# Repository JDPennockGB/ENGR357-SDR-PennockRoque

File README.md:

# ENGR 357 Pico SDR Receiver

A custom-built, high-performance Software Defined Radio (SDR) receiver powered by the Raspberry Pi Pico (RP2040). This project combines a classic hardware Tayloe detector with modern digital signal processing, streaming 24-bit I/Q audio and CAT control over a single USB cable directly to PC-based SDR software like **Quisk**.

GitHub Link: https://github.com/JDPennockGB/ENGR357-SDR-PennockRoque 

---

## Overview

Traditional homebrew SDR receivers often rely on routing analog audio cables into a PC soundcard, which can introduce noise and ground loops. This project solves that by digitizing the baseband I/Q signals directly on the board using a dedicated 24-bit ADC, and utilizing the RP2040's hardware PIO and TinyUSB stack to act as a **Composite CDC-UAC1 USB Device**. 

When plugged into a computer, this radio appears simultaneously as:
1. **USB Audio Class 2.0 (UAC2) Input:** Streaming ultra-clean 24-bit stereo I/Q audio to the PC.
2. **USB CDC Serial Port:** Receiving standard CAT tuning commands from the SDR software.

## Key Features

ADD FEATURES

---

## Hardware
### Overview
* **MCU:** Raspberry Pi Pico (RP2040) utilizing PIO and DMA for zero-jitter data handling.
* **Clock Generator:** Si5351A providing precise LO generation and the 12.288 MHz Master Clock (MCLK) for the ADC.
* **Quadrature Generator:** SN74AC74 Johnson counter for exact 90-degree I/Q phase shifting.
* **Mixer (Tayloe Detector):** SN74CBT3253 Quadrature Sampling Detector.
* **Baseband Amplification:** OPA2350 high-speed, low-noise operational amplifiers.
* **Digitization:** PCM1808 24-bit Stereo I2S ADC.
* **User Interface:** * Newhaven 1x8 Character LCD (ST7066U / 3.3V)
  * Quadrature Rotary Encoder with push-button for VFO tuning
  * 4x SMD Push Buttons for menu/mode navigation (not currently implemented in software)

### Pinout Configuration
The following table outlines the physical connections between the Raspberry Pi Pico and your hardware components.

| Pin | Function | Connected | Implemented |
| :--- | :--- | :---: | :---: |
| **GPIO0** | BCK | ✅ | ❌ |
| **GPIO1** | WS | ✅ | ❌ |
| **GPIO2** | DOUT | ✅ | ❌ |
| **GPIO11** | SD | ✅ | ❌ |
| **GPIO3** | LCD_Bit0 | ✅ | ✅ |
| **GPIO4** | LCD_Bit1 | ✅ | ✅ |
| **GPIO5** | LCD_Bit2 | ✅ | ✅ |
| **GPIO6** | LCD_Bit3 | ✅ | ✅ |
| **GPIO7** | LCD_Bit4 | ✅ | ✅ |
| **GPIO8** | LCD_Bit5 | ✅ | ✅ |
| **GPIO9** | LCD_Bit6 | ✅ | ✅ |
| **GPIO10** | LCD_Bit7 | ✅ | ✅ |
| **GPIO12** | I2C Bus SDA | ✅ | ✅ |
| **GPIO13** | I2C Bus SCL | ✅ | ✅ |
| **GPIO14** | LCD_RegSel | ✅ | ✅ |
| **GPIO15** | LCD_Ena | ✅ | ✅ |
| **GPIO16** | Up_Btn | ✅ | ❌ |
| **GPIO17** | Left_Btn | ✅ | ❌ |
| **GPIO18** | Select_Btn | ✅ | ❌ |
| **GPIO19** | Right_Btn | ✅ | ❌ |
| **GPIO20** | Encoder_A | ✅ | ✅ |
| **GPIO21** | Encoder_B | ✅ | ✅ |
| **GPIO22** | Encoder_Button| ✅ | ❌ |
| **GPIO26** | ADC0 (I_OUT) | ❌ | ❌ |
| **GPIO27** | ADC1 (Q_OUT) | ❌ | ❌ |
| **AGND** | GND | ✅ | ✅ |
| **VBUS** | +5v Bus | ✅ | ✅ |
| **3v3** | +3.3v Bus | ✅ | ✅ |

---

## Software
### Overview
* **Framework:** C/C++ via the Raspberry Pi Pico SDK.
* **USB Stack:** TinyUSB configured for a unidirectional composite UAC1 Capture + CDC interface.
* **DSP Pipeline:** Custom PIO state machines reading I2S data, fed via DMA directly to USB buffers without bottlenecking the CPU.

### Function Reference

#### LCD Driver (`lcd_driver.c`)
Manages the 8-bit parallel interface for the ST7066U controller.

| Function | Description |
| :--- | :--- |
| `void lcd_init()` | [cite_start]Executes the power-on initialization routine, including the 3-step "Wake up" sequence required for the ST7066U controller to stabilize[cite: 259]. |
| `void lcd_command(uint8_t cmd)` | Sets the `RS` (Register Select) pin LOW for command mode, drives the 8-bit bus, and toggles the `E` (Enable) pin to latch data. |
| `void lcd_clear()` | [cite_start]Sends the `0x01` instruction to clear the display RAM and reset the cursor[cite: 178]. |
| `void lcd_print(const char* str)` | Sets `RS` HIGH for data mode, iterates through the string, and writes character bytes to the LCD data bus. |

#### Clock Synthesizer (`si5351.c`)
Interfaces with the Si5351 via I2C for frequency generation.

| Function | Description |
| :--- | :--- |
| `bool si5351_init(i2c_inst_t *i2c)` | [cite_start]Initializes I2C, verifies device status, and loads factory crystal load settings[cite: 172]. |
| `uint32_t si5351_set_frequency(...)` | Calculates PLL and MultiSynth divisors, programs the register blocks, resets the PLL to achieve frequency lock, and enables the output clock. |

#### Command & Control (`cdc_app.c` & `main.c`)
Handles communication and system state.

| Function | Description |
| :--- | :--- |
| `void cdc_task()` | Parses incoming serial data for Quisk-compatible commands (e.g., `FREQ`, `VER`, `XTAL`), enabling remote control of the SDR. |
| `static void process_command(const char *line)` | Dispatcher function that maps string commands (like `FREQ`) to specific hardware actions. |
| `void audio_task()` | Handles the audio buffer from the DMA/FIFO into the USB streaming interface. |
| `void encoder_callback(...)` | ISR that tracks encoder rotation to update the `current_hz` variable, which is then processed by the main loop. |

### Build Instructions
1. **Prerequisites**: Ensure the `Pico SDK` abd `TinyUSB` libraries are installed
2. **Setup**:
   ```bash
   cd /path/to/sdr-firmware
   rm -rf build && mkdir build && cd build

---

## Repository Structure

This repository contains the hardware design files, the C/C++ firmware, Python unit tests, and relevant research documentation.

ENGR-357-SDR/

├── Documents/              # Research notes, datasheets, and design requirements

├── KiCad Designs/          # PCB schematics, layout files, and BOMs

│   ├── v1 Switch Mixer/

│   ├── v2 Tayloe Detector/

│   └── v3 Tayloe Detector FINAL/

├── LT Spice Simulations/   # RF demodulator analysis and circuit models

│   ├── LTSpice project files/

│   └── Simulation Results/ # Images of simulation results

└── sdr-firmware/           # RP2040 Firmware (Pico SDK)

    ├── build/              # Compiled binaries and artifacts

    ├── PythonUnitTests/    # Verification and testing scripts

    └── main.c + drivers                # C firmware source files

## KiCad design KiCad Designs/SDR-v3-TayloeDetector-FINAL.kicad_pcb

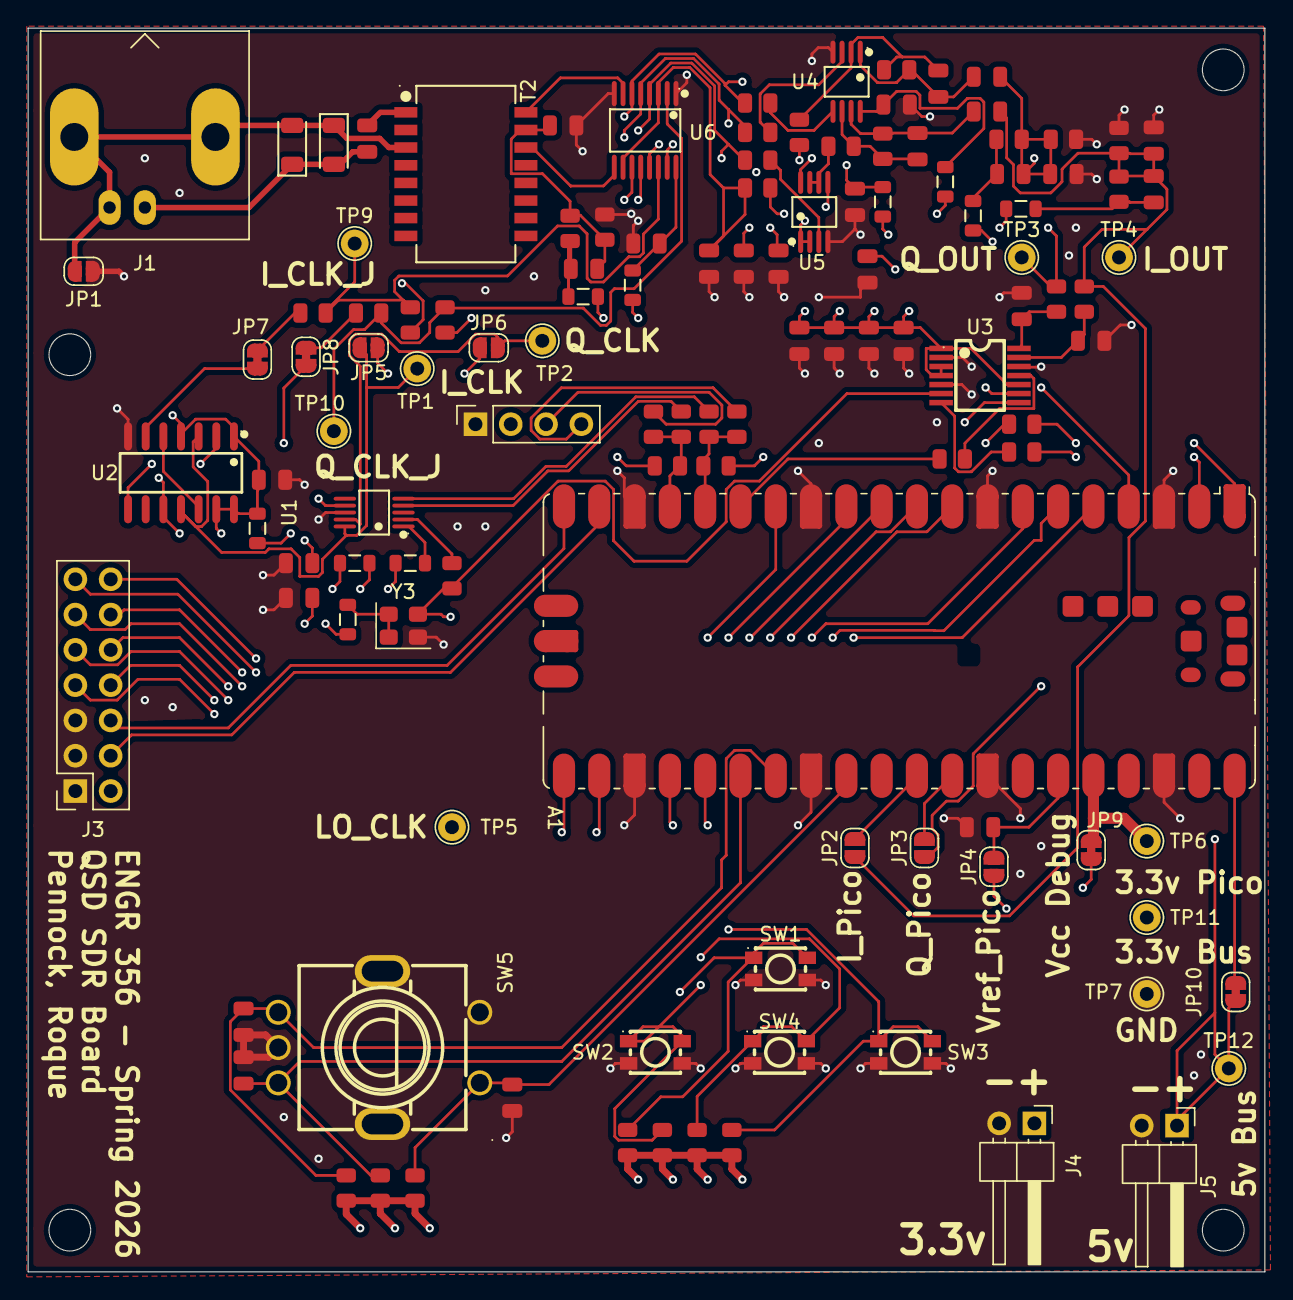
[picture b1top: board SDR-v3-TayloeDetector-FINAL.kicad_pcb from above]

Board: 4 copper layers, 89.0 x 89.5 mm, 120 parts (0 on the bottom side), 85 nets.

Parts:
A1: RaspberryPi_Pico; RaspberryPi_Pico_SMD
C1, C2, C3, C4, C9, C12, C13, C18, C19, C20, C21, C27, C29, C32, C33, C35: 10uF; C_0805
C5, C6, C7, C8: 10nF; C_0805
C10, C11: 47pF; C_0805
C16, C17: 1uF; C_0805
C23, C24, C28, C30, C31: 100nF; C_0805
C25, C34: 2.2nF; C_0805
D1, D2: 1N4004W; D_SOD-123FL
FB11, FB12, FB13, FB14, FB15, FB16, FB17, FB18, FB19, FB20: FB_0805
J1: Antenna; BNC_Amphenol_B6252HB-NPP3G-50_Horizontal
J2: OLED Header; PinSocket_1x04_P2.54mm_Vertical
J3: 1x8 LCD Header; PinSocket_2x07_P2.54mm_Vertical
J4, J5: BackupVCC (+3.3v); PinHeader_1x02_P2.54mm_Horizontal
JP1: Antenna2GND; SolderJumper-2_P1.3mm_Open_RoundedPad1.0x1.5mm
JP2: I2PicoADC; SolderJumper-2_P1.3mm_Open_RoundedPad1.0x1.5mm
JP3: Q2PicoADC; SolderJumper-2_P1.3mm_Open_RoundedPad1.0x1.5mm
JP4: PicoADCVref; SolderJumper-2_P1.3mm_Open_RoundedPad1.0x1.5mm
JP5: I_CLK_nonJ; SolderJumper-2_P1.3mm_Open_RoundedPad1.0x1.5mm
JP6: Q_CLK_nonJ; SolderJumper-2_P1.3mm_Open_RoundedPad1.0x1.5mm
JP7: I_CLK_Johnson; SolderJumper-2_P1.3mm_Bridged_RoundedPad1.0x1.5mm
JP8: Q_CLK_Johnson; SolderJumper-2_P1.3mm_Bridged_RoundedPad1.0x1.5mm
JP9: 3.3v_Pico2Bus; SolderJumper-2_P1.3mm_Bridged_RoundedPad1.0x1.5mm
JP10: 5vPicoBus; SolderJumper-2_P1.3mm_Bridged_RoundedPad1.0x1.5mm
R1, R2, R3, R4: 10Ω; R_0805
R5, R6: 47Ω; R_0805
R7, R8: 1.5kΩ; R_0805
R9, R10, R11, R12, R13, R14, R16, R24: 33Ω; R_0805
R15, R23: 470Ω; R_0805
R17, R18, R19, R20: 100Ω; R_0805
R21, R22: 4.7kΩ; R_0805
R36, R37, R38, R39, R40, R41, R42, R43, R44, R45, R46, R47, R48: 10kΩ; R_0805
SW1, SW2, SW3, SW4: TS-1185-W-4P-H1.8-160; SW-SMD_4P-L3.5-W3.0-P1.50-LS4.7
SW5: EC11E18244AU; SW-TH_EC11XXXXXXXX
T2: H1102NLT_C20623173; XFMR-SMD_H1102NLT
TP1: I_CLK; TestPoint_THTPad_D2.0mm_Drill1.0mm
TP2: Q_CLK; TestPoint_THTPad_D2.0mm_Drill1.0mm
TP3: Q_OUT; TestPoint_THTPad_D2.0mm_Drill1.0mm
TP4: I_OUT; TestPoint_THTPad_D2.0mm_Drill1.0mm
TP5: LO_CLK; TestPoint_THTPad_D2.0mm_Drill1.0mm
TP6: +3.3V_Pico; TestPoint_THTPad_D2.0mm_Drill1.0mm
TP7: GND; TestPoint_THTPad_D2.0mm_Drill1.0mm
TP9: I_CLK_J; TestPoint_THTPad_D2.0mm_Drill1.0mm
TP10: Q_CLK_J; TestPoint_THTPad_D2.0mm_Drill1.0mm
TP11: +3.3V_bus; TestPoint_THTPad_D2.0mm_Drill1.0mm
TP12: +5V_bus; TestPoint_THTPad_D2.0mm_Drill1.0mm
U1: SI5351A-B-GT; MSOP-10_L3.0-W3.0-P0.50-LS5.0-BL
U2: SN74AC74DR; SOIC-14_L8.7-W3.9-P1.27-LS6.0-BL
U3: PCM1808PWR; TSSOP-14_L5.0-W4.4-P0.65-LS6.4-BL
U4, U5: OPA2350EA/250; VSSOP-8_L3.0-W3.0-P0.65-LS5.0-BL
U6: SN74CBT3253DBQR; SSOP-16_L4.9-W3.9-P0.64-LS6.0-BL
Y3: ASE-xxxMHz; Oscillator_SMD_Abracon_ASE-4Pin_3.2x2.5mm

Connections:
+3.3V: C27.2, C28.1, C29.2, C30.1, C32.2, C33.2, FB11.1, FB13.1, FB14.1, FB15.1, FB16.1, FB17.1, FB18.1, FB19.1, FB20.1, J2.2, J3.2, J4.1, JP4.1 (A), JP9.1 (A), R21.1, R22.1, R42.2, R43.2, R44.2, R45.2, R46.2, R47.2, R48.2, TP11.1 (1_1), U3.1 (VREF), U3.3 (VCC), U3.4 (VDD), U3.10 (MD0)
+5V: FB12.1, J5.1, JP10.2 (B), TP12.1 (1_1)
/BCK: A1.1 (GPIO0), R10.2
/DOUT: A1.4 (GPIO2), U3.9 (DOUT)
/Enc_A: A1.26 (GPIO20), C24.1, R47.1, SW5.B
/Enc_B: A1.27 (GPIO21), C23.1, R48.1, SW5.A
/Enc_Sw: A1.29 (GPIO22), C31.1, R46.1, SW5.E
/GPIO12: A1.16 (GPIO12), R17.2, R20.2, R22.2
/GPIO13: A1.17 (GPIO13), R18.2, R19.2, R21.2
/I_CLK: R11.2, R16.1, TP9.1 (1_1), U6.14 (S0)
/I_OUT: C17.2, C20.2, C21.2, JP2.1 (A), R15.1, R40.2, R41.1, TP4.1 (1_1)
/LCD_Bit0: A1.5 (GPIO3), J3.7
/LCD_Bit1: A1.6 (GPIO4), J3.8
/LCD_Bit2: A1.7 (GPIO5), J3.9
/LCD_Bit3: A1.9 (GPIO6), J3.10
/LCD_Bit4: A1.10 (GPIO7), J3.11
/LCD_Bit5: A1.11 (GPIO8), J3.12
/LCD_Bit6: A1.12 (GPIO9), J3.13
/LCD_Bit7: A1.14 (GPIO10), J3.14
/LCD_Ena: A1.20 (GPIO15), J3.6
/LCD_RegSel: A1.19 (GPIO14), J3.4
/LO_CLK: R13.1, TP5.1 (1_1), U3.6 (SCKI), Y3.3 (OUT)
/Left_Btn: A1.22 (GPIO17), R43.1, SW2.1, SW2.2
/OSC_SCL: R18.1, U1.4 (SCL)
/OSC_SDA: R17.1, U1.5 (SDA)
/Q_CLK: R12.2, R24.2, TP10.1 (1_1), U6.2 (S1)
/Q_OUT: C16.2, C18.1, C19.1, JP3.1 (A), R23.1, R36.2, R39.1, TP3.1 (1_1)
/Right_Btn: A1.25 (GPIO19), R44.1, SW3.1, SW3.2
/SCL: J2.3, R19.1
/SD: A1.15 (GPIO11), R9.2
/SDA: J2.4, R20.1
/Select_Btn: A1.24 (GPIO18), R45.1, SW4.1, SW4.2
/Up_Btn: A1.21 (GPIO16), R42.1, SW1.1, SW1.2
/WS: A1.2 (GPIO1), R14.2
GND: A1.3 (GND), A1.8 (GND), A1.13 (GND), A1.18 (GND), A1.23 (GND), A1.28 (GND), A1.33 (AGND), A1.38 (GND), C3.2, C4.2, C5.2, C6.2, C7.2, C8.2, C9.2, C12.2, C13.2, C19.2, C20.1, C23.2, C24.2, C25.2, C27.1, C28.2, C29.1, C30.2, C31.2, C32.1, C33.1, C34.2, C35.1, J2.1, J3.1, J3.3, J3.5, J4.2, J5.2, JP1.2 (B), R38.2, R39.2, R40.1, SW1.3, SW1.4, SW2.3, SW2.4, SW3.3, SW3.4, SW4.3, SW4.4, SW5.6, SW5.7, SW5.C, SW5.D, TP7.1 (1_1), U1.8 (GND), U2.7 (GND), U3.2 (AGND), U3.5 (DGND), U3.12 (FMT), U4.4 (V-), U5.4 (V-), U6.1 (~1OE), U6.8 (GND), U6.15 (~2OE), Y3.2 (GND)
unnamed: A1.36 (3V3), JP9.2 (B), TP6.1 (1_1)
unnamed: A1.35 (ADC_VREF), C35.2, JP4.2 (B)
unnamed: A1.31 (GPIO26_ADC0), JP2.2 (B)
unnamed: A1.32 (GPIO27_ADC1), JP3.2 (B)
unnamed: A1.40 (VBUS), JP10.1 (A)
unnamed: C1.2, T2.1
unnamed: C2.1, C3.1, R37.2, R38.1, T2.15
unnamed: C2.2, FB11.2, R37.1
unnamed: C10.2, C16.1, R7.2, U4.1
unnamed: C11.2, C17.1, R8.2, U4.7
unnamed: C18.2, FB15.2, R36.1
unnamed: C21.1, FB16.2, R41.2
unnamed: D1.1, D2.2, J1.2 (Ext), JP1.1 (A), T2.3
unnamed: C1.1, D1.2, D2.1, J1.1 (In)
unnamed: JP5.1 (A), R11.1
unnamed: JP5.2 (B), TP1.1 (1_1), U1.10 (CLK0), U2.3 (1CLK), U2.11 (2CLK)
unnamed: JP6.1 (A), R12.1
unnamed: JP6.2 (B), TP2.1 (1_1), U1.9 (CLK1)
unnamed: JP7.1 (A), R16.2
unnamed: JP7.2 (B), U2.6 (~1Q)
unnamed: JP8.1 (A), R24.1
unnamed: JP8.2 (B), U2.2 (1D), U2.8 (~2Q)
unnamed: FB18.2, U1.1 (VDD)
unnamed: FB19.2, U1.7 (VDDO)
unnamed: R13.2, U1.2 (XA)
unnamed: U2.5 (1Q), U2.12 (2D)
unnamed: C13.1, FB20.2, U2.1 (~1CLR), U2.4 (~1PRE), U2.10 (~2PRE), U2.13 (~2CLR), U2.14 (VCC)
unnamed: R10.1, U3.8 (BCK)
unnamed: R14.1, U3.7 (LRCK)
unnamed: R9.1, U3.11 (MD1)
unnamed: C25.1, R15.2, U3.13 (VINL)
unnamed: C34.1, R23.2, U3.14 (VINR)
unnamed: R2.2, U4.3 (+)
unnamed: C10.1, R5.2, R7.1, U4.2 (-)
unnamed: R1.2, U4.5 (+)
unnamed: C11.1, R6.2, R8.1, U4.6 (-)
unnamed: C12.1, FB14.2, U4.8 (V+)
unnamed: R3.2, U5.3 (+)
unnamed: R5.1, U5.1, U5.2 (-)
unnamed: R4.2, U5.5 (+)
unnamed: R6.1, U5.6 (-), U5.7
unnamed: C9.1, FB13.2, U5.8 (V+)
unnamed: T2.16, U6.7 (1A)
unnamed: C5.1, R1.1, U6.6 (1B1), U6.13 (2B4)
unnamed: C6.1, R2.1, U6.5 (1B2), U6.12 (2B3)
unnamed: C7.1, R3.1, U6.4 (1B3), U6.11 (2B2)
unnamed: C8.1, R4.1, U6.3 (1B4), U6.10 (2B1)
unnamed: T2.14, U6.9 (2A)
unnamed: C4.1, FB12.2, U6.16 (VCC)
unnamed: FB17.2, Y3.1 (EN), Y3.4 (Vdd)

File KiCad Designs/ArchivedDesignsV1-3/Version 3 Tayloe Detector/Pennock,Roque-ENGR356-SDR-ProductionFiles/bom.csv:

Designator,Footprint,Quantity,Value,LCSC Part #
A1,RaspberryPi_Pico_SMD,1,RaspberryPi_Pico,C7203002
"C1, C12, C13, C18, C19, C2, C20, C21, C27, C29, C3, C32, C33, C35, C4, C9",C_0805,16,10uF,C440198
"C10, C11",C_0805,2,47pF,C14857
"C16, C17",C_0805,2,1uF,C28323
"C23, C24, C28, C30, C31",C_0805,5,100nF,C28233
"C25, C34",C_0805,2,2.2nF,C28260
"C5, C6, C7, C8",C_0805,4,10nF,C1710
"D1, D2",D_SOD-123FL,2,1N4004W,C18199087
"FB11, FB12, FB13, FB14, FB15, FB16, FB17, FB18, FB19, FB20",FB_0805,10,~,C1017
J1,BNC_Amphenol_B6252HB-NPP3G-50_Horizontal,1,Antenna,
J2,PinSocket_1x04_P2.54mm_Vertical,1,OLED Header,
J3,PinSocket_2x07_P2.54mm_Vertical,1,1x8 LCD Header,
"J4, J5",PinHeader_1x02_P2.54mm_Horizontal,2,BackupVCC (+3.3v),
"R1, R2, R3, R4",R_0805,4,10Ω,C17415
"R10, R11, R12, R13, R14, R16, R24, R9",R_0805,8,33Ω,C17634
"R15, R23",R_0805,2,470Ω,C17710
"R17, R18, R19, R20",R_0805,4,100Ω,C17408
"R21, R22",R_0805,2,4.7kΩ,C17673
"R36, R37, R38, R39, R40, R41, R42, R43, R44, R45, R46, R47, R48",R_0805,13,10kΩ,C17414
"R5, R6",R_0805,2,47Ω,C17714
"R7, R8",R_0805,2,1.5kΩ,C4310
"SW1, SW2, SW3, SW4",SW-SMD_4P-L3.5-W3.0-P1.50-LS4.7,4,TS-1185-W-4P-H1.8-160,C51927445
SW5,SW-TH_EC11XXXXXXXX,1,EC11E18244AU,C202365
T2,XFMR-SMD_H1102NLT,1,H1102NLT_C20623173,C20623173
TP1,TestPoint_THTPad_D2.0mm_Drill1.0mm,1,I_CLK,
TP10,TestPoint_THTPad_D2.0mm_Drill1.0mm,1,Q_CLK_J,
TP11,TestPoint_THTPad_D2.0mm_Drill1.0mm,1,+3.3V_bus,
TP12,TestPoint_THTPad_D2.0mm_Drill1.0mm,1,+5V_bus,
TP2,TestPoint_THTPad_D2.0mm_Drill1.0mm,1,Q_CLK,
TP3,TestPoint_THTPad_D2.0mm_Drill1.0mm,1,Q_OUT,
TP4,TestPoint_THTPad_D2.0mm_Drill1.0mm,1,I_OUT,
TP5,TestPoint_THTPad_D2.0mm_Drill1.0mm,1,LO_CLK,
TP6,TestPoint_THTPad_D2.0mm_Drill1.0mm,1,+3.3V_Pico,
TP7,TestPoint_THTPad_D2.0mm_Drill1.0mm,1,GND,
TP9,TestPoint_THTPad_D2.0mm_Drill1.0mm,1,I_CLK_J,
U1,MSOP-10_L3.0-W3.0-P0.50-LS5.0-BL,1,SI5351A-B-GT,C529366
U2,SOIC-14_L8.7-W3.9-P1.27-LS6.0-BL,1,SN74AC74DR,C352945
U3,TSSOP-14_L5.0-W4.4-P0.65-LS6.4-BL,1,PCM1808PWR,C55513
"U4, U5",VSSOP-8_L3.0-W3.0-P0.65-LS5.0-BL,2,OPA2350EA/250,C115876
U6,SSOP-16_L4.9-W3.9-P0.64-LS6.0-BL,1,SN74CBT3253DBQR,C2674552
Y3,Oscillator_SMD_Abracon_ASE-4Pin_3.2x2.5mm,1,ASE-xxxMHz,C52204801

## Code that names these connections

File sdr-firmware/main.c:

/**
 * SDR Controller - Main Firmware
 * Pinout Configured: DOUT=GPIO2, SD=GPIO11, LCD=GPIO3-10,14,15
 */

  // fixed verson for new drivers

#include <stdio.h>
#include <string.h>
#include <stdint.h>
#include "pico/stdlib.h"
#include "pico/multicore.h"
#include "hardware/pio.h"
#include "hardware/dma.h"
#include "hardware/irq.h"
#include "hardware/i2c.h"
#include "tusb.h"
#include "bsp/board.h"
#include "i2s_rx.pio.h"
#include "si5351.h"
#include "lcd_driver.h"
#include "class/audio/audio_device.h"

// --- Hardware Pins ---
#define ENC_A_PIN    20
#define ENC_B_PIN    21
#define LED_PIN      25
#define I2C_SDA_PIN  12
#define I2C_SCL_PIN  13
#define I2S_DATA_PIN 2    // DOUT
#define I2S_BCK_PIN  0
#define I2S_WS_PIN   1

// --- State Variables ---
static volatile uint32_t current_hz = 5680000; 
static volatile bool frequency_changed = true;
static bool sentinel_sent = false;

static uint8_t  s_audio_alt      = 0;
static uint32_t s_sample_rate_hz = 48000U;
static uint8_t  s_mute[3]        = {0, 0, 0}; 

// --- DMA & Audio Buffers ---
#define SINGLE_BUFFER_SIZE  768             
#define WORDS_PER_BUF       (SINGLE_BUFFER_SIZE / 4)  
static uint32_t buf_a[WORDS_PER_BUF];
static uint32_t buf_b[WORDS_PER_BUF];
static uint dma_chan_a, dma_chan_b;

// --- ISRs ---
static void __not_in_flash_func(dma_handler)(void) {
    const uint32_t *filled_buf;
    if (dma_channel_get_irq0_status(dma_chan_a)) {
        dma_channel_acknowledge_irq0(dma_chan_a);
        filled_buf = buf_a;
        dma_channel_set_write_addr(dma_chan_a, buf_a, false);
    } else if (dma_channel_get_irq0_status(dma_chan_b)) {
        dma_channel_acknowledge_irq0(dma_chan_b);
        filled_buf = buf_b;
        dma_channel_set_write_addr(dma_chan_b, buf_b, false);
    } else return;
    multicore_fifo_push_timeout_us((uint32_t)(uintptr_t)filled_buf, 0);
}

void encoder_callback(uint gpio, uint32_t events) {
    if (gpio == ENC_A_PIN) {
        if (gpio_get(ENC_B_PIN)) current_hz += 40000;
        else current_hz -= 40000;
        frequency_changed = true;
    }
}

// --- Tasks ---
static void core1_entry(void) {
    multicore_fifo_drain();               
    irq_clear(DMA_IRQ_0);
    dma_channel_set_irq0_enabled(dma_chan_a, true);
    dma_channel_set_irq0_enabled(dma_chan_b, true);
    irq_set_exclusive_handler(DMA_IRQ_0, dma_handler);
    irq_set_enabled(DMA_IRQ_0, true);
    dma_channel_start(dma_chan_a);        
    while (true) { tight_loop_contents(); }
}

static void audio_task(void) {
    uint32_t ptr_val = 0;
    if (multicore_fifo_pop_timeout_us(0, &ptr_val) && ptr_val != 0) {
        uint32_t *src = (uint32_t *)(uintptr_t)ptr_val;
        for (int i = 0; i < WORDS_PER_BUF; i++) src[i] &= 0xFFFFFF00; 
        if (s_audio_alt == 1) tud_audio_write(src, SINGLE_BUFFER_SIZE);
    }
}

void cdc_task(void) {
    if (!tud_cdc_connected()) { sentinel_sent = false; return; }
    if (!sentinel_sent) { 
        tud_cdc_write("SDR ready\n", 10);
        tud_cdc_write_flush();
        sentinel_sent = true; 
    }
}

int main(void) {
    // Replace board_init(); with:
    stdio_init_all();
    tusb_init();

    lcd_init();
    i2c_init(i2c0, 400 * 1000);
    gpio_set_function(I2C_SDA_PIN, GPIO_FUNC_I2C);
    gpio_set_function(I2C_SCL_PIN, GPIO_FUNC_I2C);
    si5351_init(i2c0);

    gpio_init(ENC_A_PIN); gpio_pull_up(ENC_A_PIN);
    gpio_init(ENC_B_PIN); gpio_pull_up(ENC_B_PIN);
    gpio_set_irq_enabled_with_callback(ENC_A_PIN, GPIO_IRQ_EDGE_RISE, true, &encoder_callback);

    PIO pio = pio0;
    uint offset = pio_add_program(pio, &i2s_rx_program);
    // Your pins are: BCK=0, WS=1, DOUT=2. The base pin is 0.
// PIO will automatically assign: base+0=BCK, base+1=WS, base+2=DOUT.
    i2s_rx_program_init(pio, 0, offset, 0);
    dma_chan_a = dma_claim_unused_channel(true);
    dma_chan_b = dma_claim_unused_channel(true);
    
    dma_channel_config c = dma_channel_get_default_config(dma_chan_a);
    channel_config_set_transfer_data_size(&c, DMA_SIZE_32);
    channel_config_set_read_increment(&c, false);
    channel_config_set_write_increment(&c, true);
    channel_config_set_dreq(&c, pio_get_dreq(pio, 0, false));
    dma_channel_configure(dma_chan_a, &c, buf_a, &pio->rxf[0], WORDS_PER_BUF, false);
    
    // ... Repeat for dma_chan_b ...

    multicore_launch_core1(core1_entry);

    while (1) {
        tud_task();    
        cdc_task();    
        audio_task();  

        // Inside while(1) loop in main.c
        gpio_put(LED_PIN, 1);
        sleep_ms(500);
        gpio_put(LED_PIN, 0);
        sleep_ms(500);

        tud_task();
        cdc_task();
        audio_task();

        if (frequency_changed) {
            // Keep the oscillator running at the 4x frequency
            si5351_set_frequency(i2c0, SI5351_CLK0, current_hz, SI5351_INTEGER_APPROX, SI5351_CLK_NONE);
            
            // Calculate the actual tuned frequency for the display (divided by 4)
            uint32_t display_hz = current_hz / 4;
            
            // Format the string (convert Hz to kHz)
            char buf[16];
            snprintf(buf, sizeof(buf), "%4d kHz", (int)(display_hz / 1000));
            
            // Print to the LCD
            lcd_clear();
            lcd_print(buf); 
            frequency_changed = false;
        }
    }
}

// --- Audio Callbacks ---
bool tud_audio_set_itf_cb(uint8_t rhport, tusb_control_request_t const *p_request) { (void)rhport; s_audio_alt = (uint8_t)(p_request->wValue & 0xFF); return true; }
bool tud_audio_set_itf_close_ep_cb(uint8_t rhport, tusb_control_request_t const *p_request) { return true; }
bool tud_audio_get_req_ep_cb(uint8_t rhport, tusb_control_request_t const *p_request) { return false; }
bool tud_audio_set_req_ep_cb(uint8_t rhport, tusb_control_request_t const *p_request, uint8_t *pBuff) { return true; }
bool tud_audio_get_req_entity_cb(uint8_t rhport, tusb_control_request_t const *p_request) { return false; }
bool tud_audio_set_req_entity_cb(uint8_t rhport, tusb_control_request_t const *p_request, uint8_t *pBuff) { return true; }

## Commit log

2026-05-21 Added v1 of board; Switch mixer design.
2026-05-21 Rename SDR-v1-SwitchMixer.kicad_pcb to KiCad Designs/Version 1 Switch Mixer/SDR-v1-SwitchMixer.kicad_pcb
2026-05-21 File structure fixes
    Fixed broken file structure
2026-05-21 Fixed file corruption
2026-05-21 Added milestone docs
2026-05-21 Added amp stage simulation
2026-05-29 Added unit test code
    Added unit test code
2026-06-01 cp $PICO_SDK_PATH/external/pico_sdk_import.cmake .
2026-06-01 Initial commit: scaffolded project structure for Pico SDR
2026-06-01 Added build files and new code structure
2026-06-03 Finished lab 7
2026-06-04 Added new project files
2026-06-04 Failed attempt to get UAC1 detection
2026-06-04 More verbose USB Device descriptors
2026-06-04 FIXED UAC1 AUDIO DEVICE - MAC/LINUX VERIFIED
2026-06-05 Encoder + USB Audio Works
2026-06-05 Added .py test files; added lcd driver; reverted to working UAC1 code
2026-06-05 fixes to pio
2026-06-06 Attempt to fix kicad files and added schematic pdf to documents folder
2026-06-06 added fix attempt for kicad file
2026-06-07 FInished Inital Hardware Documentation
2026-06-07 Unified folder names
2026-06-07 Added clean schematic
2026-06-10 Added voltage and clock verification to documentation with photos
2026-06-10 Updated documentation to align with milestones from D2L
2026-06-10 fixed file structure for milestones
2026-06-10 fixed LCD output to match johnson counter, not si5351
2026-06-10 added more photos to .ipynb documentation
2026-06-10 fixes to images in .ipynb
2026-06-10 Updated sdr-firmware to be in stable and "most-working" state
2026-06-10 Updated photos for UAC1 detection
2026-06-10 added working sdr pictures
2026-06-10 added documentation of working SDR
2026-06-10 re-added .ipynb status
2026-06-10 finished documentation
2026-06-10 added github link to top of documentation
2026-06-10 Added software overview presentation
2026-06-10 updated lcd_driver and presentation
2026-06-10 added unit test overview to presentation
2026-06-10 fixed README project structure layout
2026-06-10 fixed photo in presentation
2026-06-10 Added design hurdle of having to switch designs at the end of April
2026-06-10 rescaled for presentation on TV
2026-06-10 Added in fixed names for voltage analysis
2026-06-10 Added more improvements
